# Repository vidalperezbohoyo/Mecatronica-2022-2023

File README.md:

# Mecatronica-2022-2023

Este repositorio personal, refleja los distintos conocimientos adquiridos  
en la asignatura de Mecatrónica en la URJC en el curso 2022-2023.

He decidido organizar el repositorio por carpetas. Siendo **L2**, **L3**, **L4** ... las distintas pruebas y experimentos con lo aprendido en los días de clase.
En la wiki se puede ver información sobre mi y el comentario y desarrollo de las prácricas en esta asignatura a modo de bitácora personal.

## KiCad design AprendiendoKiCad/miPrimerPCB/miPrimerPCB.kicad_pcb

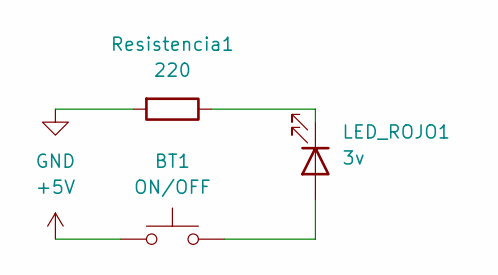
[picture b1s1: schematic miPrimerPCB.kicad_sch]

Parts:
BT1: ON/OFF; SW_PUSH_6mm
LED_ROJO1: 3v; LED_D3.0mm_FlatTop
Resistencia1: 220; R_Axial_DIN0207_L6.3mm_D2.5mm_P10.16mm_Horizontal

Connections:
+5V: BT1.1
GND: Resistencia1.2
unnamed: BT1.2, LED_ROJO1.2 (A)
unnamed: LED_ROJO1.1 (K), Resistencia1.1

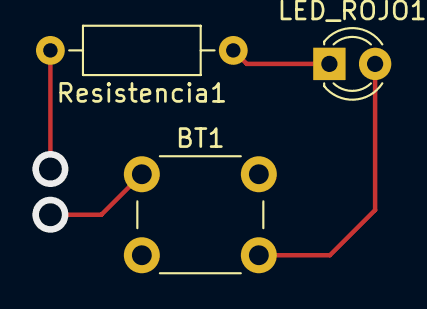
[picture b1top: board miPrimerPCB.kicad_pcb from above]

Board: 2 copper layers, 3 parts (0 on the bottom side), 2 nets.

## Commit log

2022-09-20 Readme actualizado
2022-09-20 Empezando con las pruebas de markdown
2022-09-20 Mas pruebas usando el metalenguaje Markdown
2022-09-28 Aprendiendo Svg
2022-09-28 Añadiendo cositas de KiCad
2022-10-02 Reto 2
2022-10-07 PikaPika?Pikaaa
2022-10-07 Me olvide de nariz de pikaxu
2022-10-10 Aprendiendo FreeCad
2022-10-10 Doc added
